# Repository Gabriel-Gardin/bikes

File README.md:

# bikes
Projeto rastreamento bikes CTU

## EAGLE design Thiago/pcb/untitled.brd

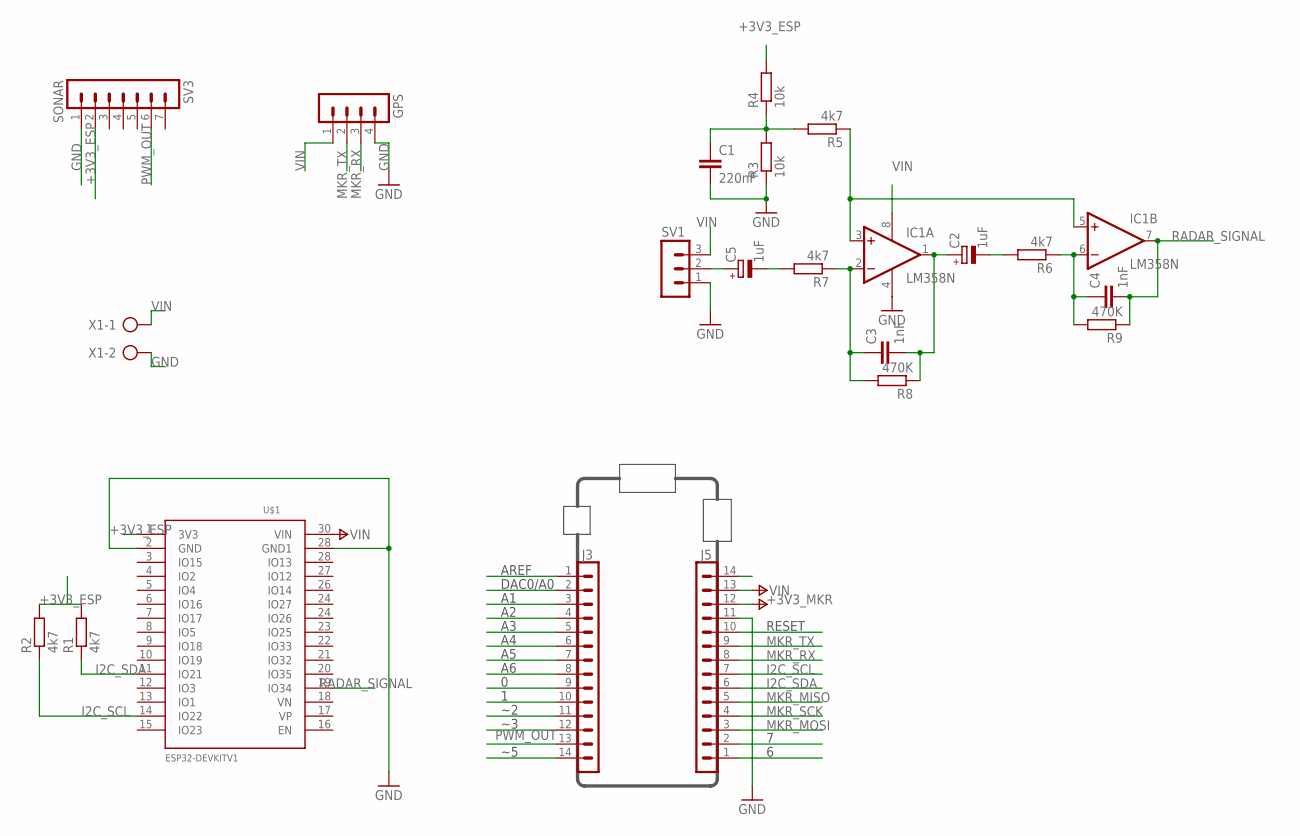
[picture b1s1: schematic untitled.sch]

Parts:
C1: 220nF; C025-025X050
C2, C5: 1uF; E2-4
C3, C4: 1nF; C025-025X050
GPS: MA04-1
IC1: LM358N; DIL08
J3, J5: -; 1X14_SMD_TH
R1, R2, R5, R6, R7: 4k7; 0207/10
R3, R4: 10k; 0207/10
R8, R9: 470K; 0207/2V
SV1: MA03-1
SV3: SONAR; MA07-1
U$1: ESP32DEVKITV1; ESP32-DEVKITV1
X1: AK500/2-H

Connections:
+3V3_ESP: R1.2, R2.2, R4.2, SV3.2, U$1.1 (3V3)
+3V3_MKR: J5.12
GND: C1.2, GPS.4, IC1.4 (V-), J5.11, R3.1, SV1.1, SV3.1, U$1.2 (GND), U$1.28 (IO13), X1.2
I2C_SCL: J5.7, R2.1, U$1.14 (IO22)
I2C_SDA: J5.6, R1.1, U$1.11 (IO21)
MKR_MISO: J5.5
MKR_MOSI: J5.3
MKR_RX: GPS.3, J5.8
MKR_SCK: J5.4
MKR_TX: GPS.2, J5.9
unnamed: C1.1, R3.2, R4.1, R5.2
unnamed: C2.-, R6.2
unnamed: IC1.3 (+IN), IC1.5 (+IN), R5.1
unnamed: C4.1, IC1.6 (-IN), R6.1, R9.2
unnamed: C5.-, R7.2
unnamed: C5.+, SV1.2
unnamed: C3.1, IC1.2 (-IN), R7.1, R8.2
unnamed: C2.+, C3.2, IC1.1 (OUT), R8.1
PA02_AIN0: J3.2
PA03_VREFA: J3.1
PA04_AIN4: J3.5
PA05_AIN5: J3.6
PA06_AIN6: J3.7
PA07_AIN7: J3.8
PA10_TCC0-W2: J3.11
PA11_TCC0-W3: J3.12
PA20_TCC0-W6: J5.1
PA21_TCC0-W7: J5.2
PA22_TC4-W0: J3.9
PA23_TC4-W1: J3.10
PB02_AIN10: J3.3
PB03_AIN11: J3.4
PB11_TCC0-W5: J3.14
PWM_OUT: J3.13, SV3.6
RADAR_SIGNAL: C4.2, IC1.7 (OUT), R9.1, U$1.19 (IO34)
RESET: J5.10
VIN: GPS.1, IC1.8 (V+), J5.13, SV1.3, U$1.30 (VIN), X1.1

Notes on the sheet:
RESET
AREF
DAC0/A0

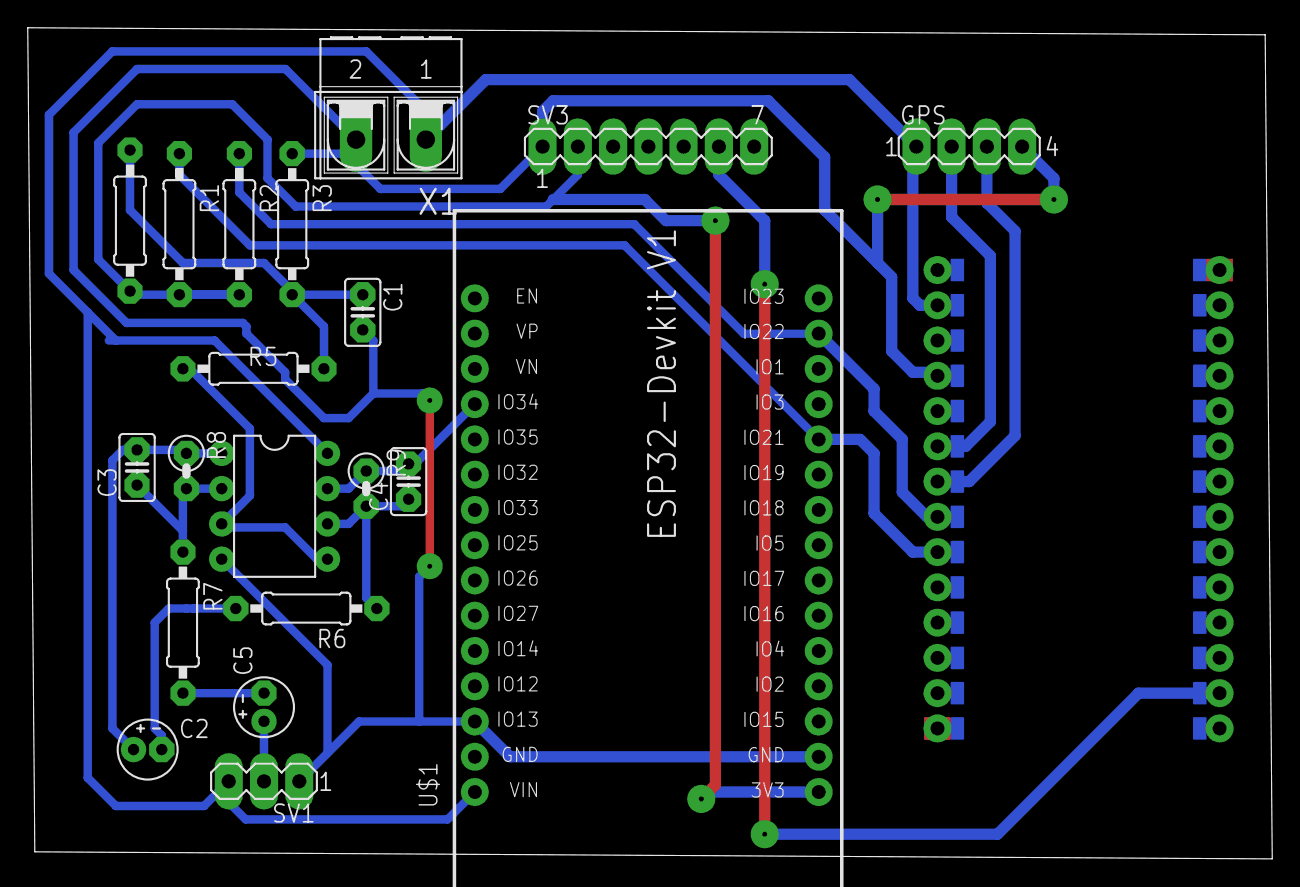
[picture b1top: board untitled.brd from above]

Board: 2 copper layers, 89.6 x 59.9 mm, 22 parts (0 on the bottom side), 17 nets.

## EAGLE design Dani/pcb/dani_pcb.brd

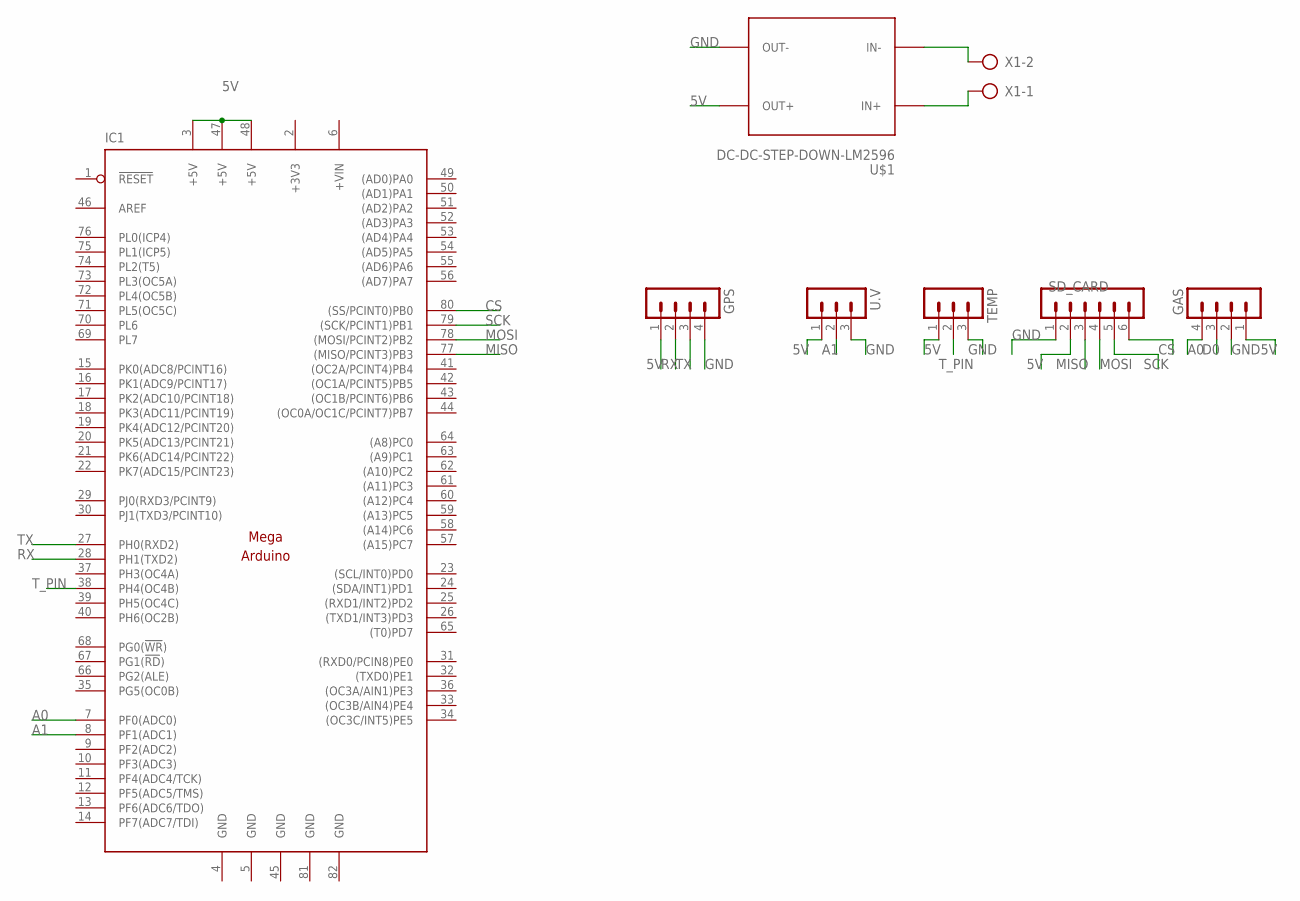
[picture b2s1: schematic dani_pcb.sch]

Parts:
GAS: MA04-1
GPS: MA04-1
IC1: MEGAARDUINO_1; MEGA_ARDUINO
SD_CARD: MA06-1
TEMP: MA03-1
U$1: DC-DC-STEP-DOWN-LM2596
U.V: MA03-1
X1: AK500/2-H

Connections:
5V: GAS.1, GPS.1, IC1.3 (+5V), IC1.47 (+5V), IC1.48 (+5V), SD_CARD.2, TEMP.1, U$1.OUT+, U.V.1
+3V3: IC1.2 (+3V3)
+VIN: IC1.6 (+VIN)
A0: GAS.4, IC1.7 (PF0(ADC0))
A1: IC1.8 (PF1(ADC1)), U.V.2
CS: IC1.80 ((SS/PCINT0)PB0), SD_CARD.6
D0: GAS.3
GND: GAS.2, GPS.4, IC1.4 (GND), IC1.5 (GND), IC1.45 (GND), IC1.81 (GND), IC1.82 (GND), SD_CARD.1, TEMP.3, U$1.OUT-, U.V.3
MISO: IC1.77 ((MISO/PCINT3)PB3), SD_CARD.3
MOSI: IC1.78 ((MOSI/PCINT2)PB2), SD_CARD.4
unnamed: U$1.IN-, X1.2
unnamed: U$1.IN+, X1.1
RX: GPS.2, IC1.28 (PH1(TXD2))
SCK: IC1.79 ((SCK/PCINT1)PB1), SD_CARD.5
TX: GPS.3, IC1.27 (PH0(RXD2))
T_PIN: IC1.38 (PH4(OC4B)), TEMP.2

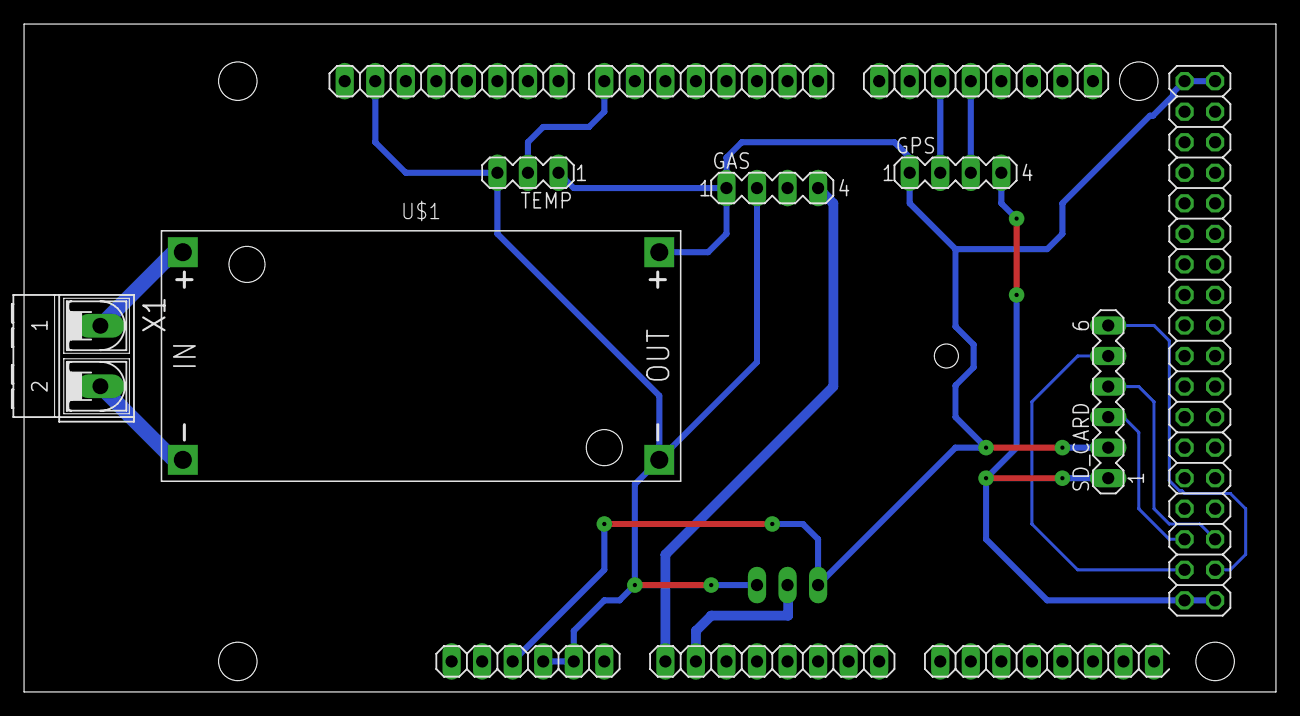
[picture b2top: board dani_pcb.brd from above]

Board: 2 copper layers, 104.1 x 55.6 mm, 8 parts (1 on the bottom side), 13 nets.

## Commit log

2019-10-10 Add documentação, converti de .ino para cpp
2019-10-10 Add lib MQTT pubsubclient
2019-10-13 MQTT, JSON, ESTÁVEL.
2019-10-13 TINYGPSplus e 6 casas decimais precisão
2019-10-13 Corrigi bugs GPS_dATA array imutável
2019-10-18 Teste_01
2019-11-01 Add, I2C, esp32 radar FFT, ...
2019-11-01 Corrigi pastas platformio
2019-11-12 Add projeto dani
2019-11-15 Add pcb dani
2019-11-16 Add arquivos pcb
2019-11-17 PCB thiago
2019-11-22 Placa thiago pronta
2019-11-28 pcbs prontas e analogRef dani
2019-11-28 Corrigi espaçãmento pcb
2019-11-28 Correçoes pcb
2019-11-28 pcbs prontas e analogRef
2019-11-28 Corrigi device esp32 eagle
2019-12-13 Add gps logger
2019-12-14 Data logger pronto
2019-12-19 Comentarios gps logger
2020-01-05 teste
2020-01-14 Radar otimizado, rm crude_Radar
2020-01-23 Updt hour Dani, sd_card radar
2020-01-23 Add time on
2020-01-24 Add identificação ao prototipo
2020-02-20 Err msg gps
2020-02-20 Salva tudo
2020-07-17 Retira delay atualização gps

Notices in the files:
parts and their libraries:
diy_modules: Released under the Creative Commons Attribution 4.0 International License: http://creativecommons.org/licenses/by/4.0
Arduino-connectors: Copyright (c) 2016-2017 Arduino LLC.  All right reserved.
